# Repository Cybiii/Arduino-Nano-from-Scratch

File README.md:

# Arduino Nano from Scratch

## Overview

This project describes a custom-designed microcontroller development board, similar to an Arduino Nano, based on the ATmega328P-M. The board integrates a stable 5V power supply, a USB-to-serial converter for programming and UART/SPI communication, and comprehensive pin headers for flexible interfacing.

<p align="center">
    
    <p align="center">Figure 1: Front view of the PCB</p>
</p>

<p align="center">
    
    <p align="center">Figure 2: Back view of the PCB</p>
</p>

## Project Architecture

The project is structured hierarchically within KiCad, with the following key sub-schematics:

1.  **Root:** The top-level schematic, connecting the main blocks.
2.  **Project Architecture:** Defines the overall system architecture.
    - **Pins:** Exposes the digital and analog I/O pins.
    - **Power Supply:** Provides a regulated 5V supply.
    - **USB Port:** Handles USB communication and power.
    - **Microcontroller:** Contains the ATmega328P-M and its supporting circuitry.

## PCB Layers

The PCB is meticulously designed with the following **4 layers** to optimize **signal integrity**, **power delivery networks (PDN)**, and **component density**, ensuring robust performance and manufacturability:

1.  **Layer Top (F.Cu - Front Copper):**

    - **Description:** This is the primary **component placement layer**, primarily accommodating **Surface Mount Devices (SMDs)** and **through-hole components**. It's strategically utilized for **critical high-speed signal routing**, **decoupling capacitor placement**, and minimizing trace lengths for **impedance control** on sensitive lines.
    - 

2.  **5V (In1.Cu - Inner Copper 1):**

    - **Description:** A dedicated **internal power plane** for the **+5V rail**. This continuous copper plane ensures **low-impedance power distribution**, minimizing **voltage ripple** and providing a robust, stable current source across the entire board, critical for **power integrity** of digital logic.
    - 

3.  **GND (In2.Cu - Inner Copper 2):**

    - **Description:** A comprehensive **internal ground plane**. This solid plane serves as a universal **low-impedance return path** for all signals, significantly reducing **electromagnetic interference (EMI)**, enhancing **electromagnetic compatibility (EMC)**, and providing effective **shielding** for sensitive traces.
    - 

4.  **Layer Bottom (B.Cu - Bottom Copper):**
    - **Description:** Utilized for completing **signal routing**, particularly for less sensitive signals or those requiring longer runs. This layer also accommodates additional **SMD component placement** and provides flexibility for **thermal management** via copper pours if needed.
    - 

## Key Components

- **U1:** ATmega328P-M Microcontroller
- **U2:** LM1117-5.0 Voltage Regulator
- **U3:** FT232RL USB-to-Serial Converter
- **J1:** USB Mini-B connector
- **J2, J4:** Main I/O Headers
- **J6, J7:** ICSP Headers

## Important Files

- `Arduino Nano.kicad_pro`: KiCad project file.
- `Arduino Nano.kicad_sch`: Top-level schematic.
- `Microcontroller.kicad_sch`, `Pins.kicad_sch`, `Power Supply.kicad_sch`, `USB Port.kicad_sch`: Hierarchical sub-schematic files.
- `Arduino Nano.kicad_pcb`: PCB layout file.
- `Arduino Nano.kicad_dru`: PCB design rules file.
- `Arduino Nano.kicad_prl`: Project-specific library settings.

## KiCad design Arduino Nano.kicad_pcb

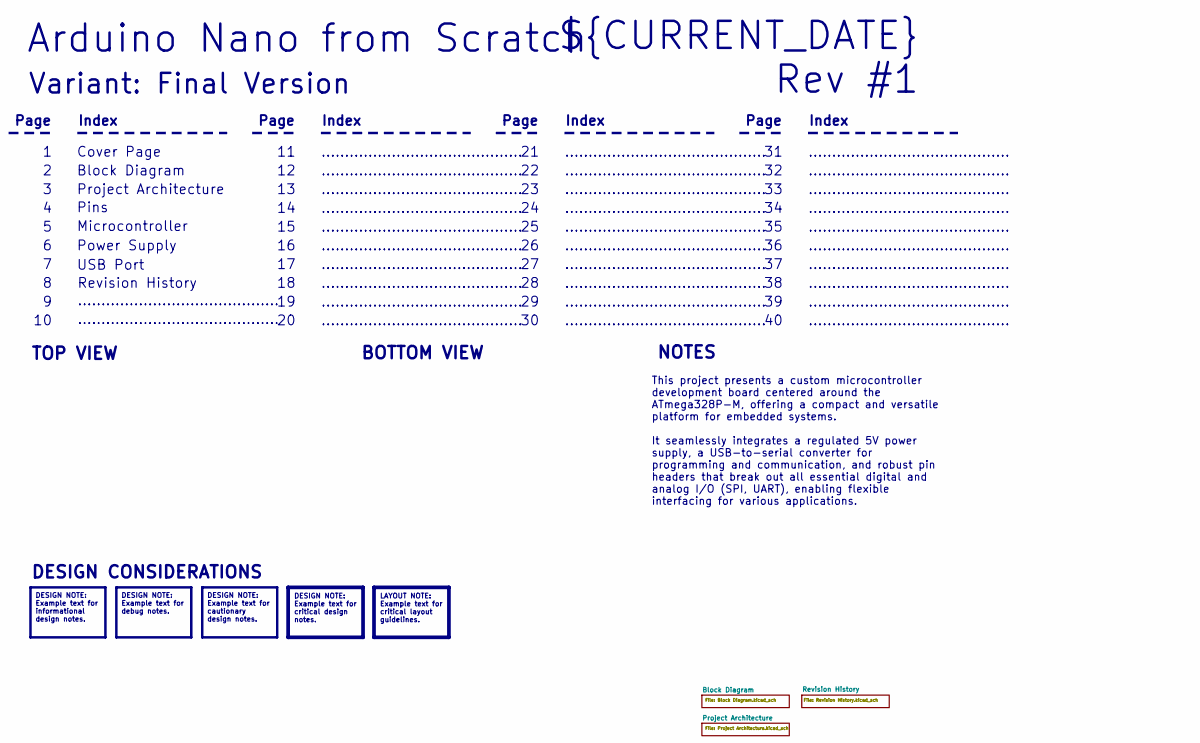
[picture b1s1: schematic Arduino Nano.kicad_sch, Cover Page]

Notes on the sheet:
BOTTOM VIEW
...........................................
Page
TOP VIEW
Power Supply
USB Port
Revision History
Index
Microcontroller
${CURRENT_DATE}
Variant: Final Version
Rev #1
Pins
Arduino Nano from Scratch
Block Diagram
Cover Page
NOTES
Project Architecture
DESIGN CONSIDERATIONS
DESIGN NOTE: Example text for informational design notes.
This project presents a custom microcontroller development board centered around the ATmega328P-M, offering a compact and versatile platform for embedded systems. It seamlessly integrates a regulated 5V power supply, a USB-to-serial converter for programming and communication, and robust pin header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
LAYOUT NOTE: Example text for critical layout guidelines.
DESIGN NOTE: Example text for cautionary design notes.
DESIGN NOTE: Example text for debug notes.
DESIGN NOTE: Example text for critical design notes.

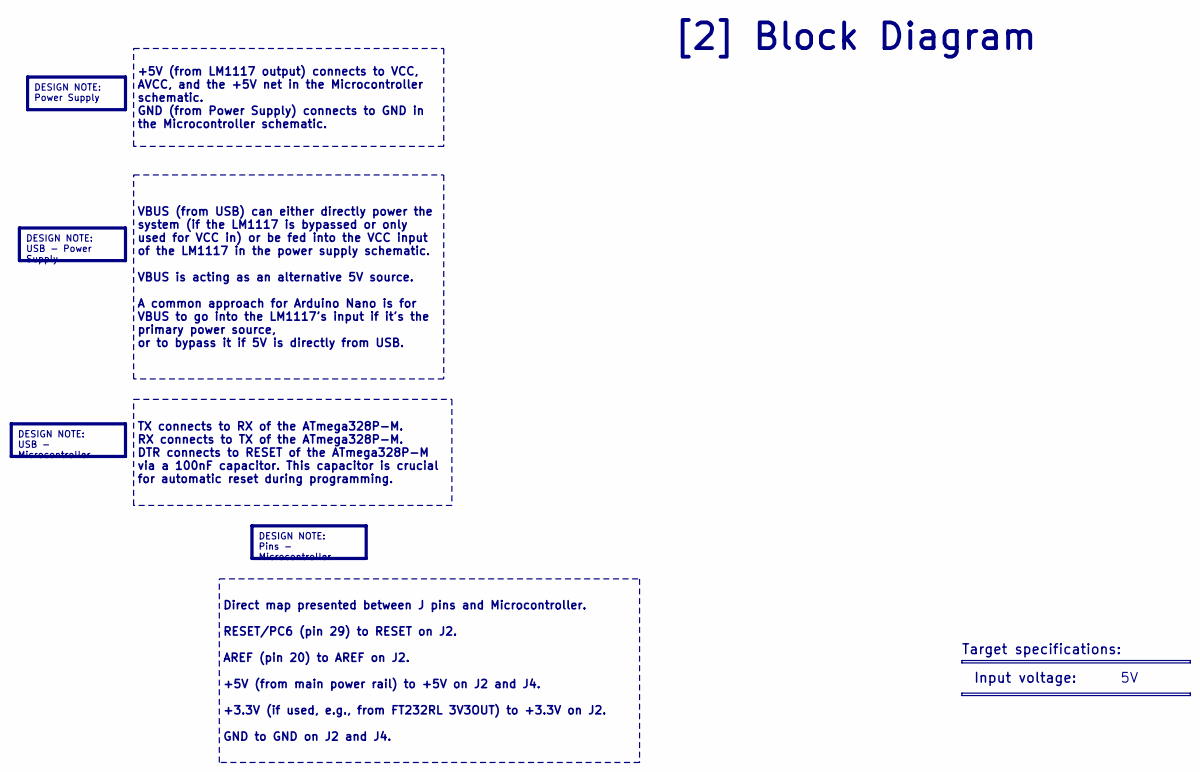
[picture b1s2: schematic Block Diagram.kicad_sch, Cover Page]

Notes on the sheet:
DESIGN NOTE: Power Supply
Input voltage:
VBUS (from USB) can either directly power the system (if the LM1117 is bypassed or only used for VCC in) or be fed into the VCC input of the LM1117 in the power supply schematic. VBUS is acting as an alternative 5V source. A common approach for Arduino Nano is for VBUS to go into the LM1117's input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
Direct map presented between J pins and Microcontroller. RESET/PC6 (pin 29) to RESET on J2. AREF (pin 20) to AREF on J2. +5V (from main power rail) to +5V on J2 and J4. +3.3V (if used, e.g., from FT232RL 3V3OUT) to +3.3V on J2. GND to GND on J2 and J4.
DESIGN NOTE: USB - Microcontroller
[2] Block Diagram
DESIGN NOTE: Pins - Microcontroller
Target specifications:
+5V (from LM1117 output) connects to VCC, AVCC, and the +5V net in the Microcontroller schematic. GND (from Power Supply) connects to GND in the Microcontroller schematic.
DESIGN NOTE: USB - Power Supply
TX connects to RX of the ATmega328P-M. RX connects to TX of the ATmega328P-M. DTR connects to RESET of the ATmega328P-M via a 100nF capacitor. This capacitor is crucial for automatic reset during programming.

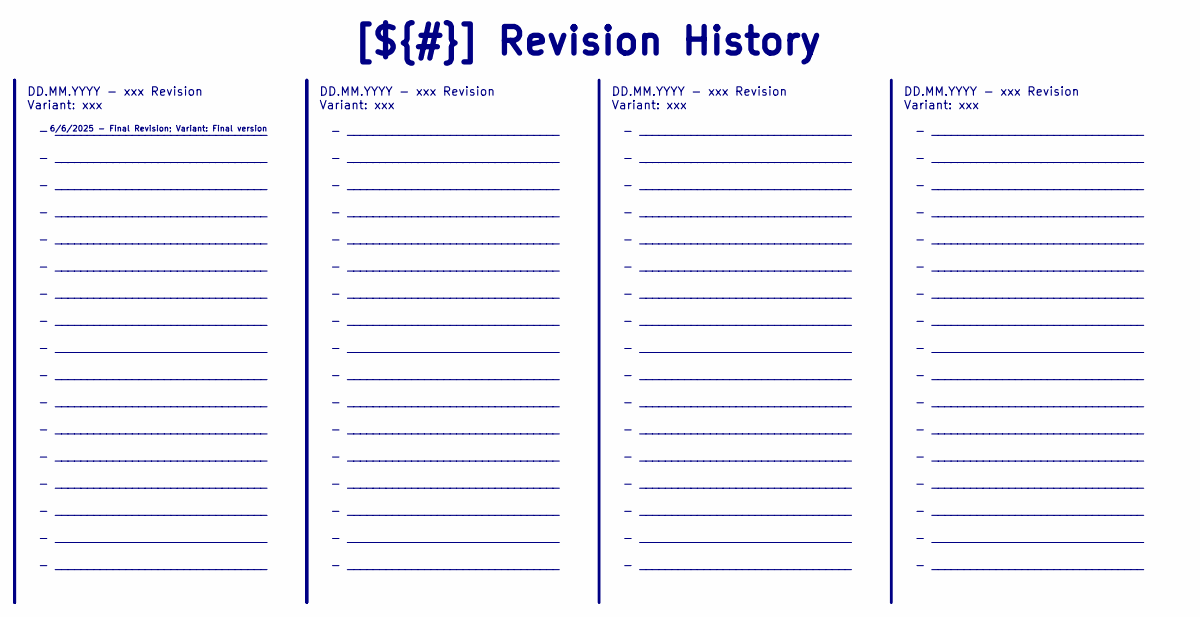
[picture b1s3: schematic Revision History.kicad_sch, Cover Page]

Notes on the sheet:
6/6/2025 - Final Revision; Variant: Final version
- _________________________________ - _________________________________ - _________________________________ - _________________________________ - _________________________________ - _________________________________ - _________________________________ - _________________________________ - _________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
DD.MM.YYYY - xxx Revision Variant: xxx
[${#}] Revision History

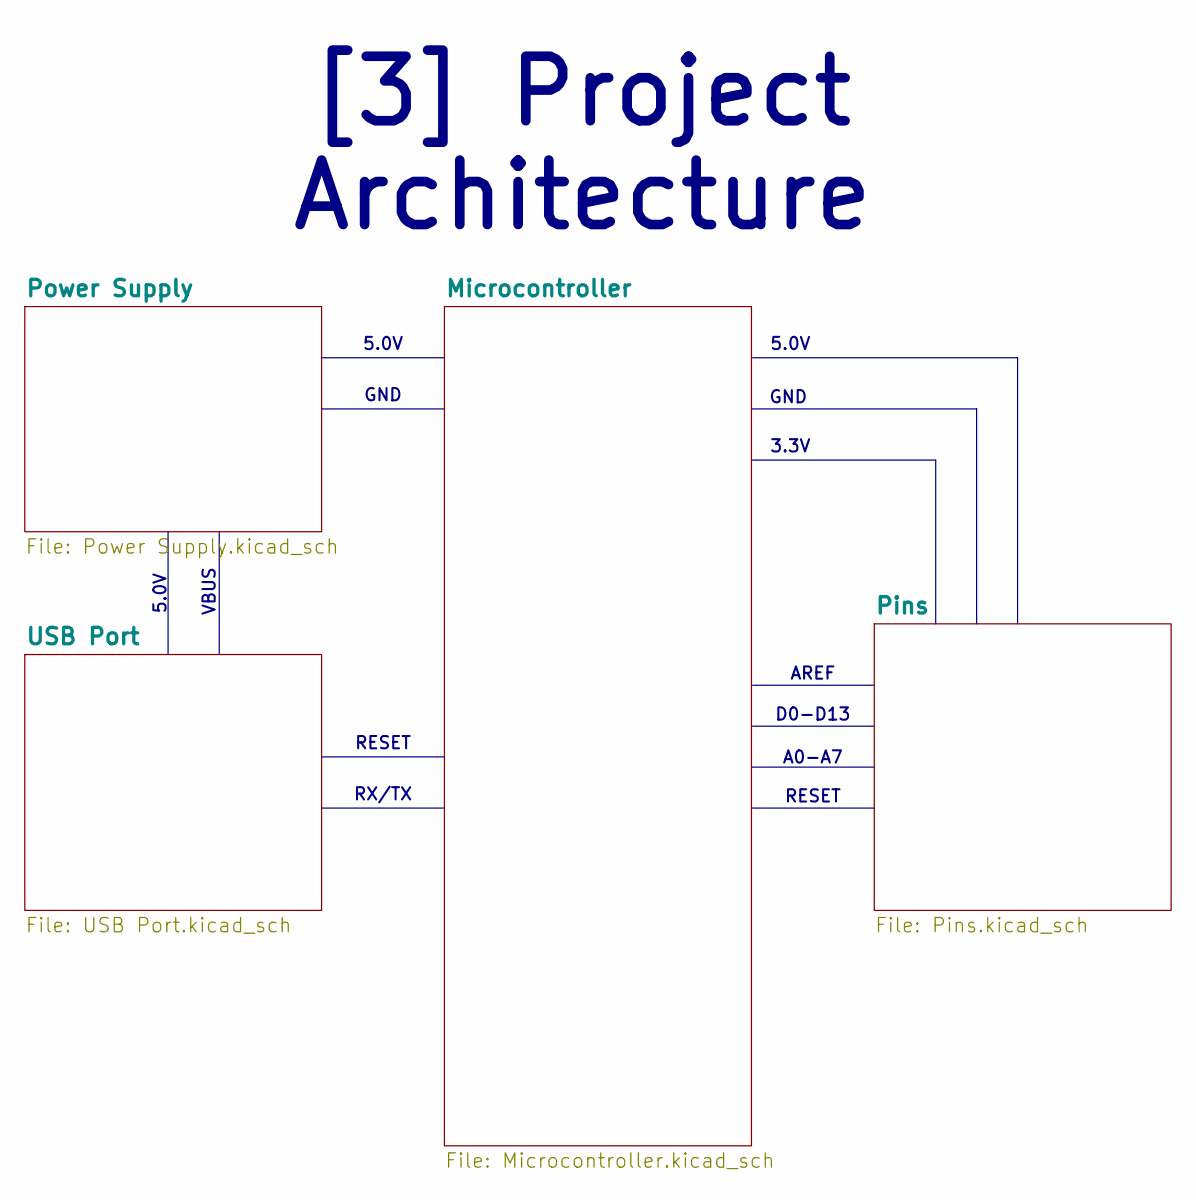
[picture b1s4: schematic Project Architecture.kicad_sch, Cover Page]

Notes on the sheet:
5.0V
VBUS
GND
3.3V
RESET
A0-A7
AREF
RX/TX
D0-D13
[3] Project Architecture

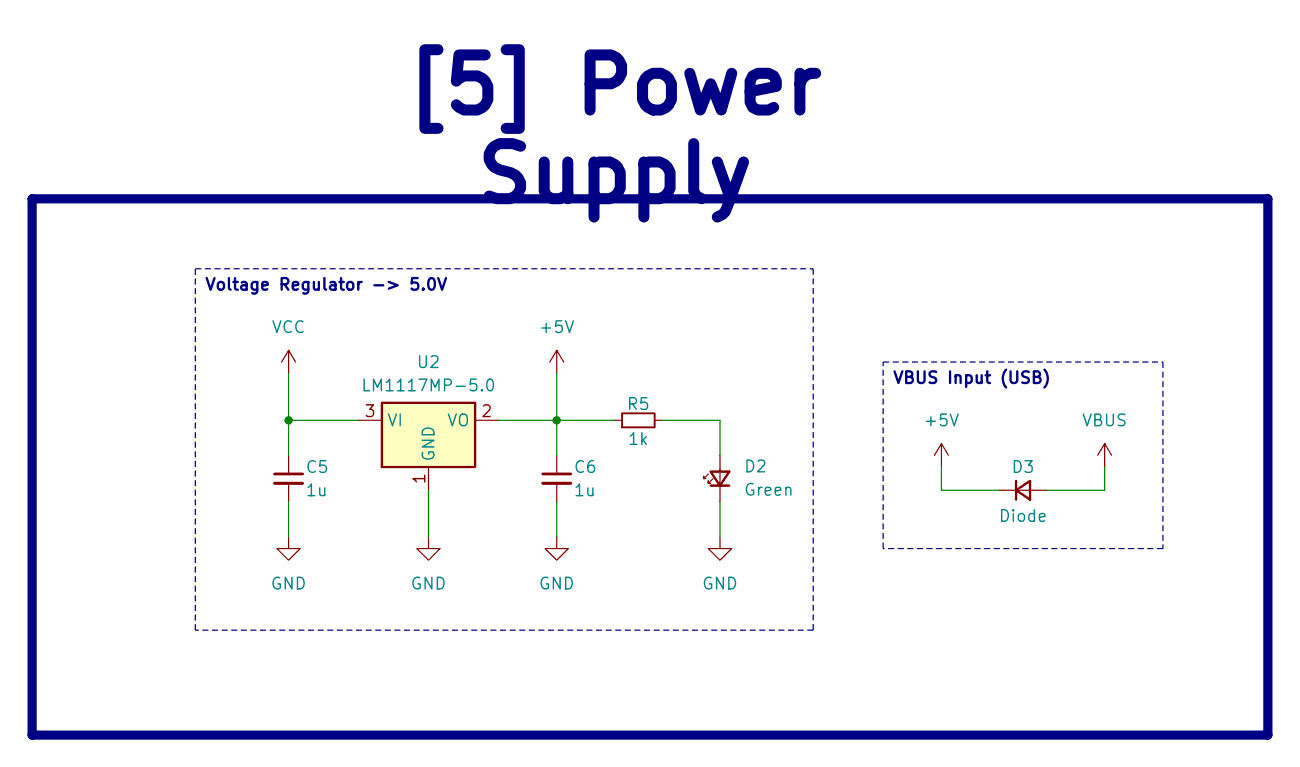
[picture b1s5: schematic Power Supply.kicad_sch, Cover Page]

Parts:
C5, C6: 1u; C_0603_1608Metric
D2: Green; LED_0805_2012Metric
D3: Diode; D_MicroSMP_AK
R5: 1k; R_0603_1608Metric
U2: LM1117MP-5.0; SOT-223-3_TabPin2

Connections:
+5V: C6.1, D3.1 (K), R5.1, U2.2 (VO); also elsewhere on the board
GND: C5.2, C6.2, D2.1 (K), U2.1 (GND); also elsewhere on the board
unnamed: D2.2 (A), R5.2
VBUS: D3.2 (A); also elsewhere on the board
VCC: C5.1, U2.3 (VI); also elsewhere on the board

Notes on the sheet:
VBUS Input (USB)
[5] Power Supply
Voltage Regulator -> 5.0V

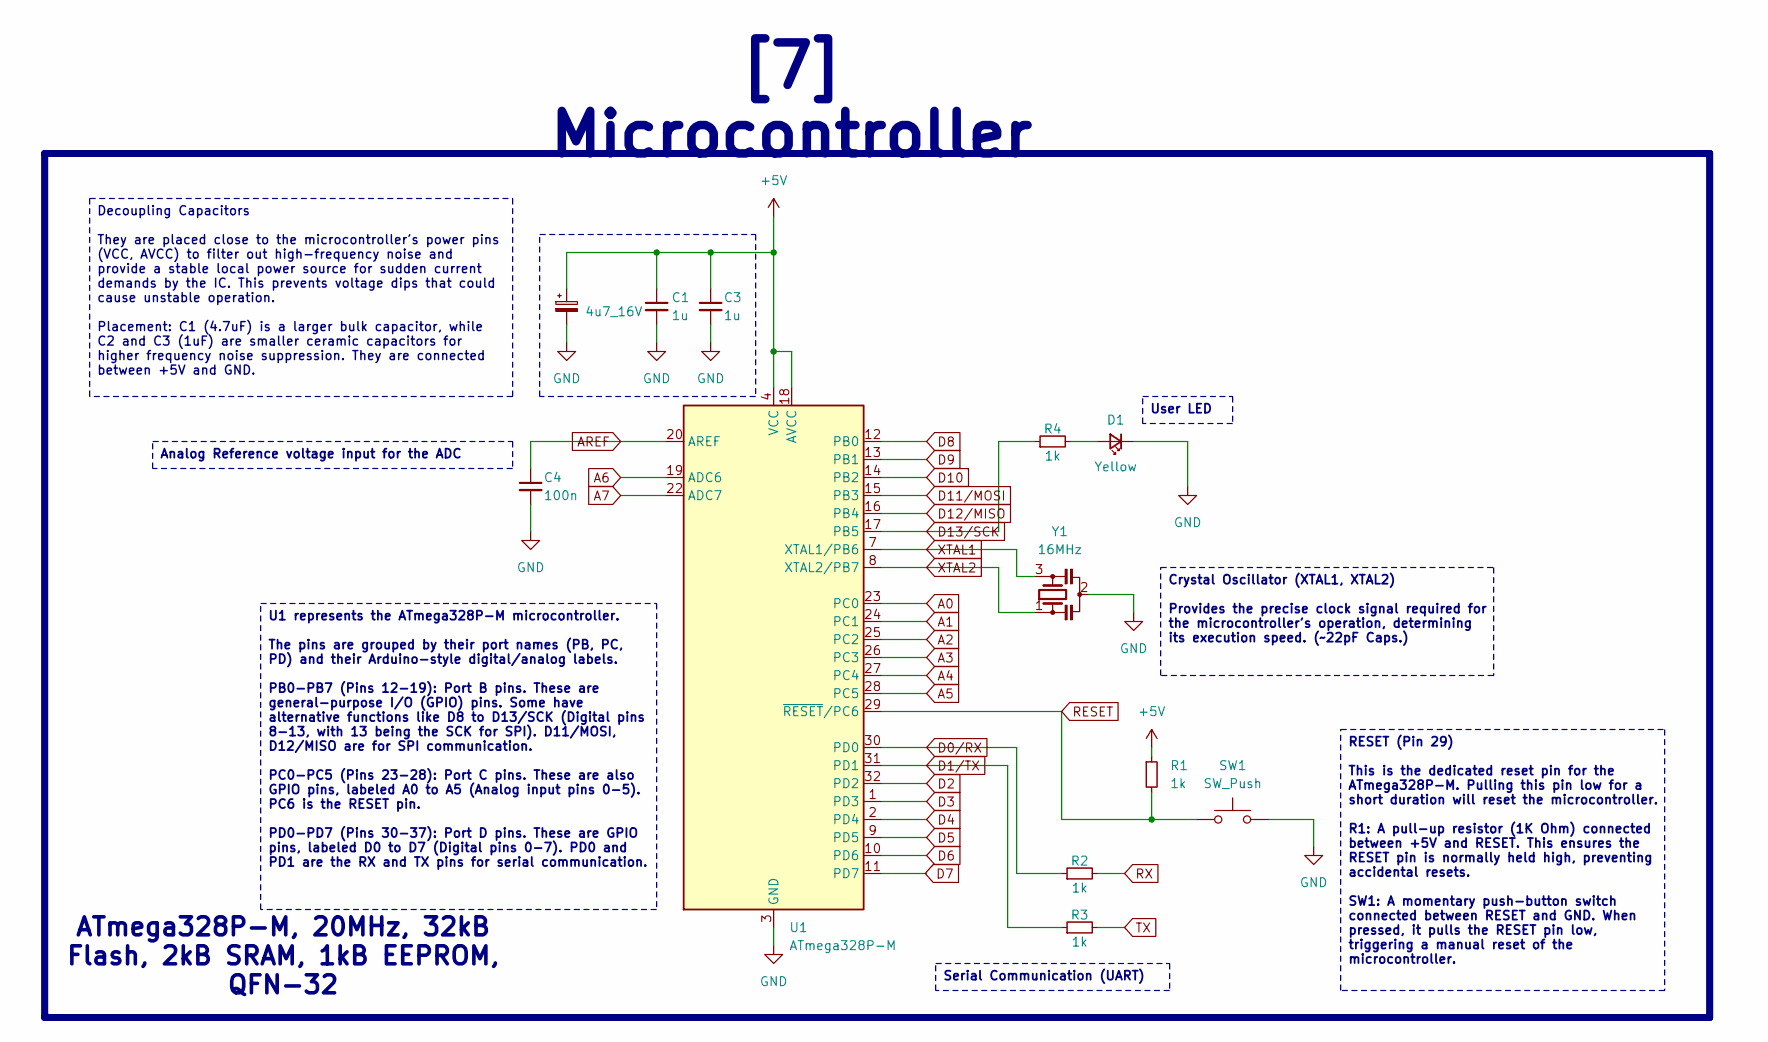
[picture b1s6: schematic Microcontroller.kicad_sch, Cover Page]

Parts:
C1, C3: 1u; C_0603_1608Metric
C2: 4u7_16V; CP_EIA-3216-10_Kemet-I
C4: 100n; C_0603_1608Metric
D1: Yellow; LED_0805_2012Metric
R1, R2, R3, R4: 1k; R_0603_1608Metric
SW1: SW_Push; Panasonic_EVQPUK_EVQPUB
U1: ATmega328P-M; QFN-32-1EP_5x5mm_P0.5mm_EP3.1x3.1mm
Y1: 16MHz; Resonator_SMD_Murata_CSTxExxV-3Pin_3.0x1.1mm

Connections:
+5V: C1.1, C2.1, C3.1, R1.1, U1.4 (VCC), U1.6 (VCC), U1.18 (AVCC); also elsewhere on the board
A0: U1.23 (PC0); also elsewhere on the board
A1: U1.24 (PC1); also elsewhere on the board
A2: U1.25 (PC2); also elsewhere on the board
A3: U1.26 (PC3); also elsewhere on the board
A4: U1.27 (PC4); also elsewhere on the board
A5: U1.28 (PC5); also elsewhere on the board
A6: U1.19 (ADC6); also elsewhere on the board
A7: U1.22 (ADC7); also elsewhere on the board
AREF: C4.1, U1.20 (AREF); also elsewhere on the board
D0/RX: R2.1, U1.30 (PD0); also elsewhere on the board
D1/TX: R3.1, U1.31 (PD1); also elsewhere on the board
D2: U1.32 (PD2); also elsewhere on the board
D3: U1.1 (PD3); also elsewhere on the board
D4: U1.2 (PD4); also elsewhere on the board
D5: U1.9 (PD5); also elsewhere on the board
D6: U1.10 (PD6); also elsewhere on the board
D7: U1.11 (PD7); also elsewhere on the board
D8: U1.12 (PB0); also elsewhere on the board
D9: U1.13 (PB1); also elsewhere on the board
D10: U1.14 (PB2); also elsewhere on the board
D11/MOSI: U1.15 (PB3); also elsewhere on the board
D12/MISO: U1.16 (PB4); also elsewhere on the board
D13/SCK: R4.1, U1.17 (PB5); also elsewhere on the board
GND: C1.2, C2.2, C3.2, C4.2, D1.1 (K), SW1.2, U1.3 (GND), U1.5 (GND), U1.21 (GND), U1.33 (GND), Y1.2; also elsewhere on the board
unnamed: D1.2 (A), R4.2
RESET: R1.2, SW1.1, U1.29 (~RESET/PC6); also elsewhere on the board
RX: R2.2; also elsewhere on the board
TX: R3.2; also elsewhere on the board
XTAL1: U1.7 (XTAL1/PB6), Y1.3
XTAL2: U1.8 (XTAL2/PB7), Y1.1

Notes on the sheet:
Crystal Oscillator (XTAL1, XTAL2) Provides the precise clock signal required for the microcontroller's operation, determining its execution speed. (~22pF Caps.)
RESET (Pin 29) This is the dedicated reset pin for the ATmega328P-M. Pulling this pin low for a short duration will reset the microcontroller. R1: A pull-up resistor (1K Ohm) connected between +5V and RESET. This ensures the RESET pin is normally held high, preventing accidental resets. SW1: A mome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
Decoupling Capacitors They are placed close to the microcontroller's power pins (VCC, AVCC) to filter out high-frequency noise and provide a stable local power source for sudden current demands by the IC. This prevents voltage dips that could cause unstable operation. Placement: C1 (4.7uF) is a lar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
[7] Microcontroller
Analog Reference voltage input for the ADC
Serial Communication (UART)
ATmega328P-M, 20MHz, 32kB Flash, 2kB SRAM, 1kB EEPROM, QFN-32
U1 represents the ATmega328P-M microcontroller. The pins are grouped by their port names (PB, PC, PD) and their Arduino-style digital/analog labels. PB0-PB7 (Pins 12-19): Port B pins. These are general-purpose I/O (GPIO) pins. Some have alternative functions like D8 to D13/SCK (Digital pins 8-13, w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
User LED

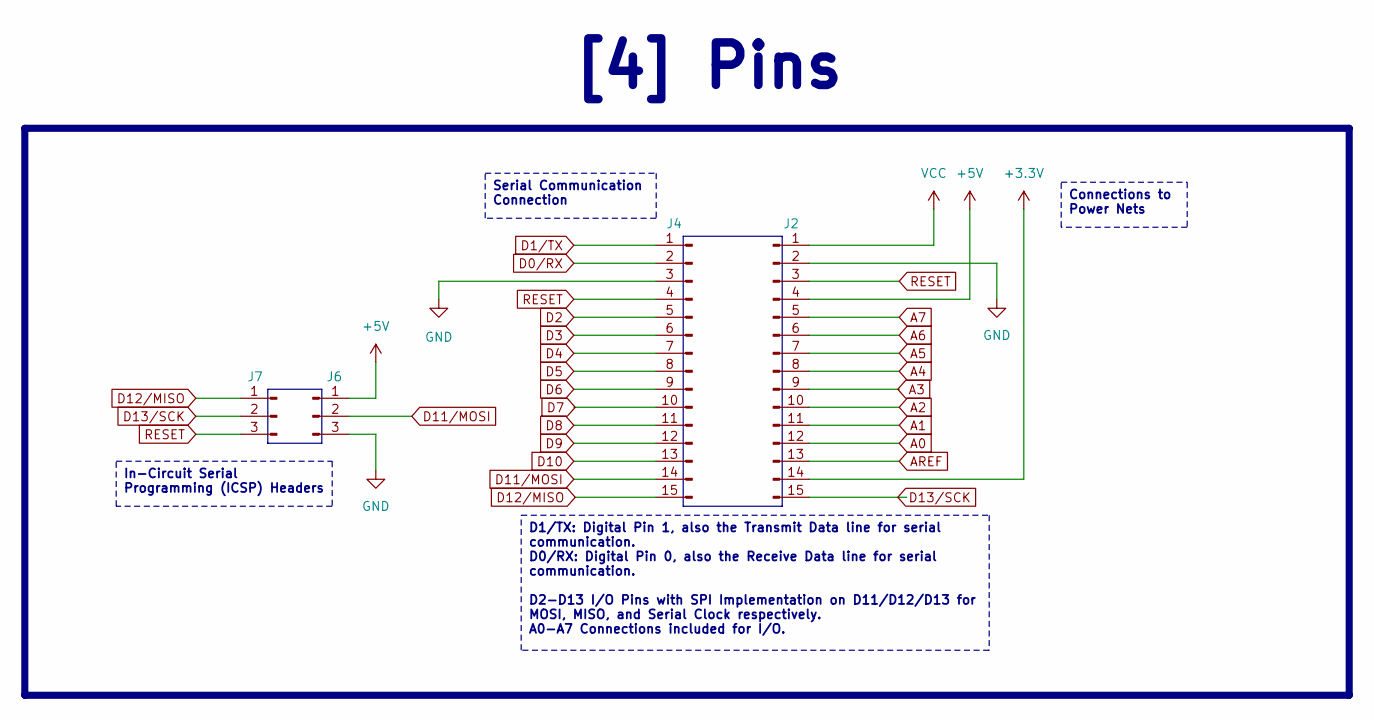
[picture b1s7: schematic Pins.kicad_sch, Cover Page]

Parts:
J2, J4: Conn_01x15_Pin; PinSocket_1x15_P2.54mm_Vertical
J6, J7: Conn_01x03_Pin; PinHeader_1x03_P2.54mm_Vertical

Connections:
+3.3V: J2.14; also elsewhere on the board
+5V: J2.4, J6.1; also elsewhere on the board
A0: J2.12; also elsewhere on the board
A1: J2.11; also elsewhere on the board
A2: J2.10; also elsewhere on the board
A3: J2.9; also elsewhere on the board
A4: J2.8; also elsewhere on the board
A5: J2.7; also elsewhere on the board
A6: J2.6; also elsewhere on the board
A7: J2.5; also elsewhere on the board
AREF: J2.13; also elsewhere on the board
D0/RX: J4.2; also elsewhere on the board
D1/TX: J4.1; also elsewhere on the board
D2: J4.5; also elsewhere on the board
D3: J4.6; also elsewhere on the board
D4: J4.7; also elsewhere on the board
D5: J4.8; also elsewhere on the board
D6: J4.9; also elsewhere on the board
D7: J4.10; also elsewhere on the board
D8: J4.11; also elsewhere on the board
D9: J4.12; also elsewhere on the board
D10: J4.13; also elsewhere on the board
D11/MOSI: J4.14, J6.2; also elsewhere on the board
D12/MISO: J4.15, J7.1; also elsewhere on the board
D13/SCK: J2.15, J7.2; also elsewhere on the board
GND: J2.2, J4.3, J6.3; also elsewhere on the board
RESET: J2.3, J4.4, J7.3; also elsewhere on the board
VCC: J2.1; also elsewhere on the board

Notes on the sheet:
D1/TX: Digital Pin 1, also the Transmit Data line for serial communication. D0/RX: Digital Pin 0, also the Receive Data line for serial communication. D2-D13 I/O Pins with SPI Implementation on D11/D12/D13 for MOSI, MISO, and Serial Clock respectively. A0-A7 Connections included for I/O.
Serial Communication Connection
In-Circuit Serial Programming (ICSP) Headers
[4] Pins
Connections to Power Nets

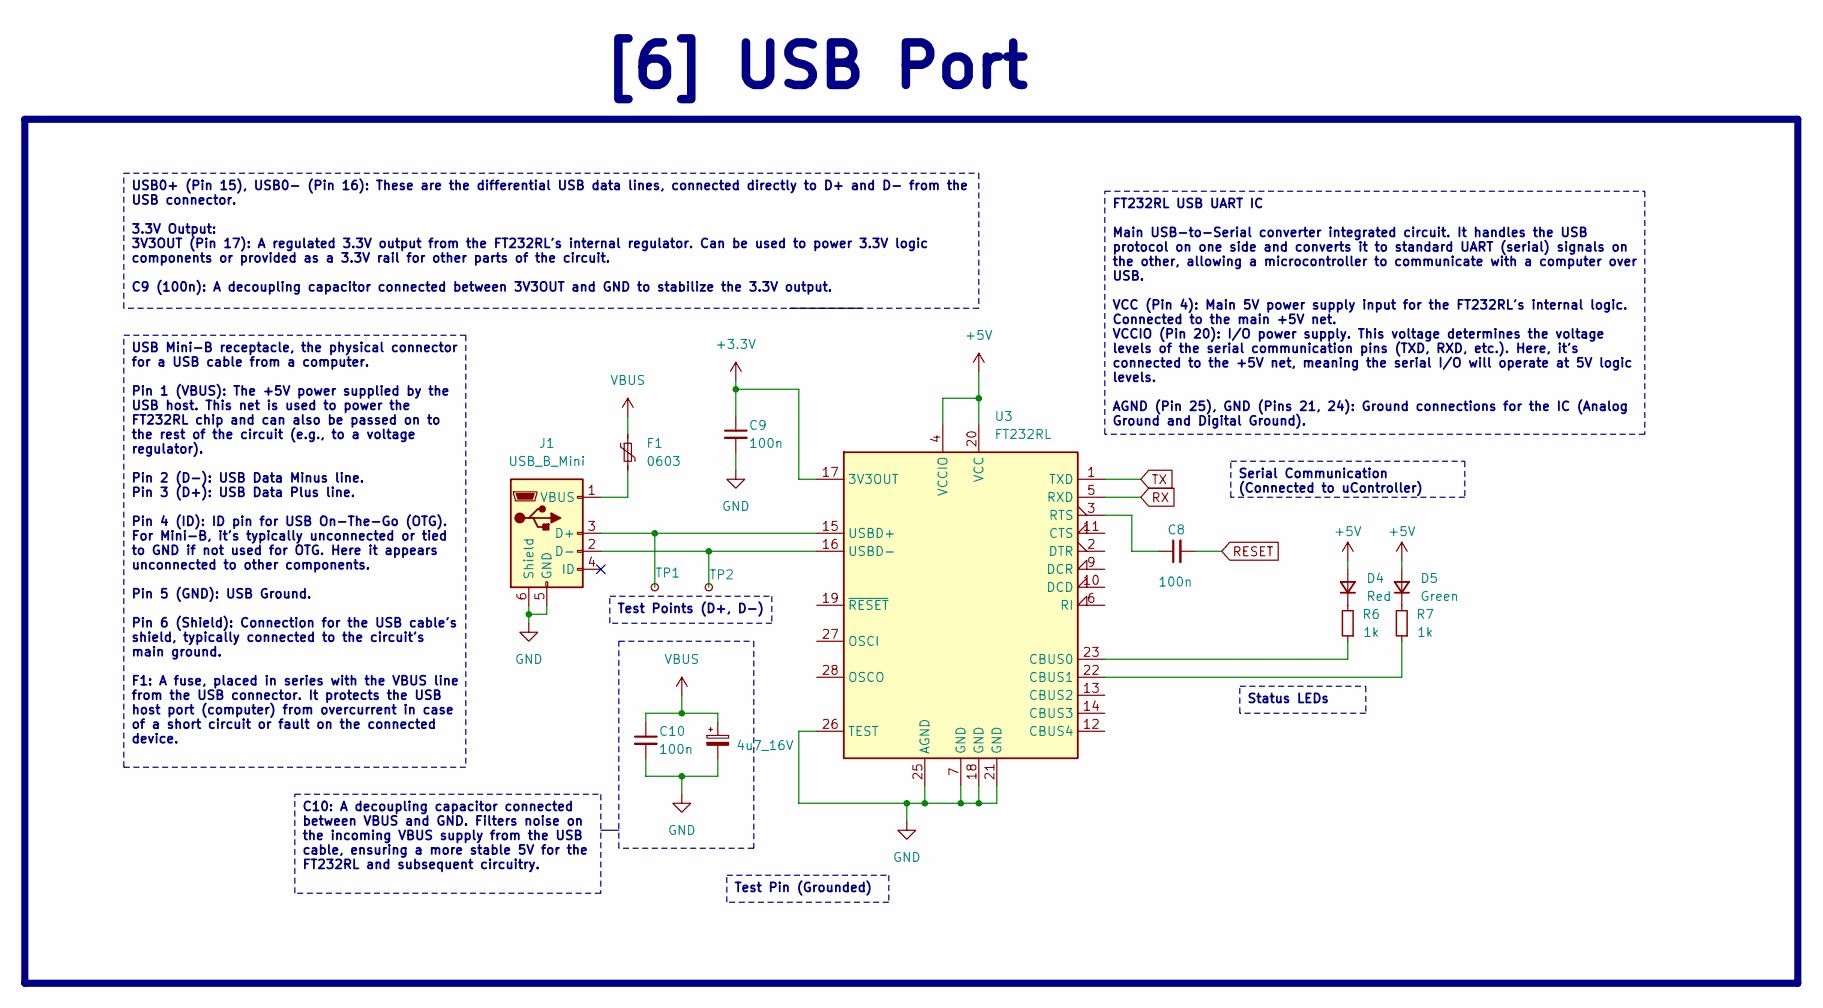
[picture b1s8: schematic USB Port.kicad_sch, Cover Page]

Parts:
C7: 4u7_16V; CP_EIA-3216-10_Kemet-I
C8, C9, C10: 100n; C_0603_1608Metric
D4: Red; LED_0805_2012Metric
D5: Green; LED_0805_2012Metric
F1: 0603; D_0603_1608Metric
J1: USB_B_Mini; USB_Mini-B_Wuerth_65100516121_Horizontal
R6, R7: 1k; R_0603_1608Metric
TP1, TP2: TestPoint_Small; TestPoint_Pad_D1.0mm
U3: FT232RL; SSOP-28_5.3x10.2mm_P0.65mm

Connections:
+3.3V: C9.1, U3.17 (3V3OUT); also elsewhere on the board
+5V: D4.2 (A), D5.2 (A), U3.4 (VCCIO), U3.20 (VCC); also elsewhere on the board
GND: C7.2, C9.2, C10.2, J1.5 (GND), J1.6 (Shield), U3.7 (GND), U3.18 (GND), U3.21 (GND), U3.25 (AGND), U3.26 (TEST); also elsewhere on the board
unnamed: D4.1 (K), R6.2
unnamed: D5.1 (K), R7.2
unnamed: J1.3 (D+), TP1.1, U3.15 (USBD+)
unnamed: J1.2 (D-), TP2.1, U3.16 (USBD-)
unnamed: F1.2, J1.1 (VBUS)
unnamed: R6.1, U3.23 (CBUS0)
unnamed: R7.1, U3.22 (CBUS1)
unnamed: C8.1, U3.3 (RTS)
RESET: C8.2; also elsewhere on the board
RX: U3.5 (RXD); also elsewhere on the board
TX: U3.1 (TXD); also elsewhere on the board
VBUS: C7.1, C10.1, F1.1; also elsewhere on the board

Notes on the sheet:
C10: A decoupling capacitor connected between VBUS and GND. Filters noise on the incoming VBUS supply from the USB cable, ensuring a more stable 5V for the FT232RL and subsequent circuitry.
Status LEDs
Test Points (D+, D-)
[6] USB Port
USB0+ (Pin 15), USB0- (Pin 16): These are the differential USB data lines, connected directly to D+ and D- from the USB connector. 3.3V Output: 3V3OUT (Pin 17): A regulated 3.3V output from the FT232RL's internal regulator. Can be used to power 3.3V logic components or provided as a 3.3V rail for o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
FT232RL USB UART IC Main USB-to-Serial converter integrated circuit. It handles the USB protocol on one side and converts it to standard UART (serial) signals on the other, allowing a microcontroller to communicate with a computer over USB. VCC (Pin 4): Main 5V power supply input for the FT232RL's 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
USB Mini-B receptacle, the physical connector for a USB cable from a computer. Pin 1 (VBUS): The +5V power supplied by the USB host. This net is used to power the FT232RL chip and can also be passed on to the rest of the circuit (e.g., to a voltage regulator). Pin 2 (D-): USB Data Minus line. Pin 3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
Serial Communication (Connected to uController)
Test Pin (Grounded)

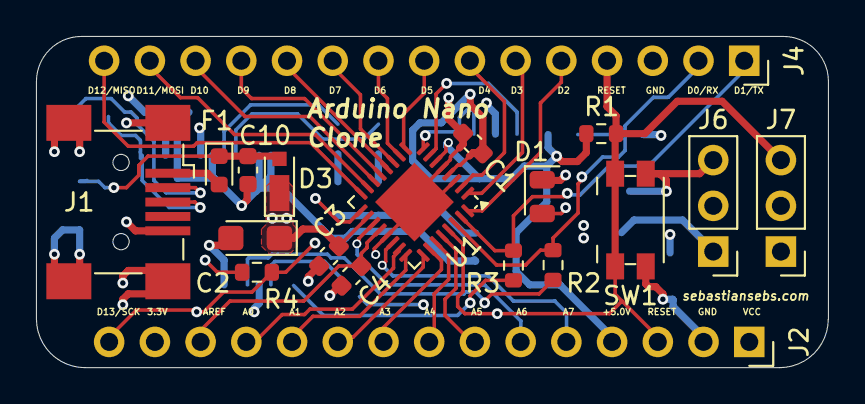
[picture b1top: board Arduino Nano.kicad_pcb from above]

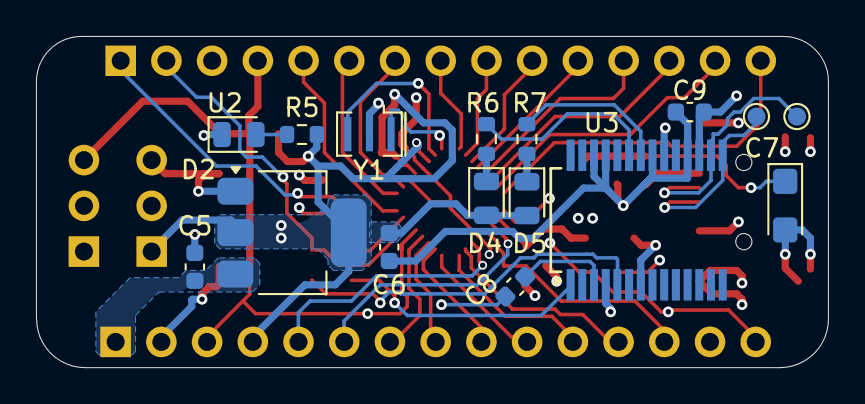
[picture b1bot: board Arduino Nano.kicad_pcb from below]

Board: 4 copper layers, 44.0 x 18.4 mm, 39 parts (16 on the bottom side), 43 nets.

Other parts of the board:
H1, H2, H3, H4: 1.6mm; MountingHole_2mm

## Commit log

2025-06-06 Arduino-Nano setup
2025-06-06 Refactoring
2025-06-06 block
